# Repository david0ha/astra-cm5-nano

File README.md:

# Astra CM5 Nano

55 × 40 mm carrier board for the Raspberry Pi Compute Module 5.

## Specifications

| Item | Specification |
|---|---|
| Board size | 55 × 40 mm |
| Copper layers | 8 |
| Board thickness | 1.5936 mm |
| Module | Raspberry Pi CM5 / CM5 Lite |
| USB-C | 5 V input and USB 2.0 device port |
| USB Type-A | USB 3.0 host port |
| CSI / DSI | Two 22-pin, four-lane ports |
| GPIO | 40-pin SMT header; 3.3 V reference by default (R16 fitted, R17 DNP). For 1.8 V, remove R16 and fit R17; never fit both. |
| microSD | For CM5 Lite |
| Auxiliary connectors | Four-pin fan and two-pin RTC battery |
| Controls and indicators | BOOT and PWR buttons; power and activity LEDs |
| Status | Not built or tested. |

## Files

| File | Location |
|---|---|
| Native KiCad project | [hardware/cm5-nano-compatible/](hardware/cm5-nano-compatible/) |
| Full schematic | [PDF](docs/exports/schematic-full.pdf) · [SVG](docs/exports/schematic-full.svg) · [PNG](docs/exports/schematic-full.png) |
| Focused schematic pages | [PDF](docs/exports/schematic-focused-pages.pdf) |
| PCB layers | [PDF](docs/exports/pcb-layers.pdf) · [SVG](docs/exports/pcb-layers/layers.svg) · [copper-layer SVGs](docs/exports/copper-layers/) |
| Bill of materials | [Detail CSV](assembly/cm5-nano-compatible-BOM-detail.csv) · [JLCPCB CSV](assembly/cm5-nano-compatible-BOM-JLCPCB.csv) |
| Component positions | [CPL CSV](assembly/cm5-nano-compatible-CPL-kicad-native.csv); KiCad-native placement coordinates, no assembler-specific adjustments |

Vendor 3D models are not included.

Open `hardware/cm5-nano-compatible/cm5-nano-compatible.kicad_pro` in KiCad 10.

Reference: [Waveshare CM5-NANO-A](https://www.waveshare.com/cm5-nano-a.htm).

## License

Original project contributions: [CERN-OHL-P-2.0](LICENSE). Third-party material retains its original terms; see [THIRD_PARTY.md](THIRD_PARTY.md) and [LICENSES/](LICENSES/).

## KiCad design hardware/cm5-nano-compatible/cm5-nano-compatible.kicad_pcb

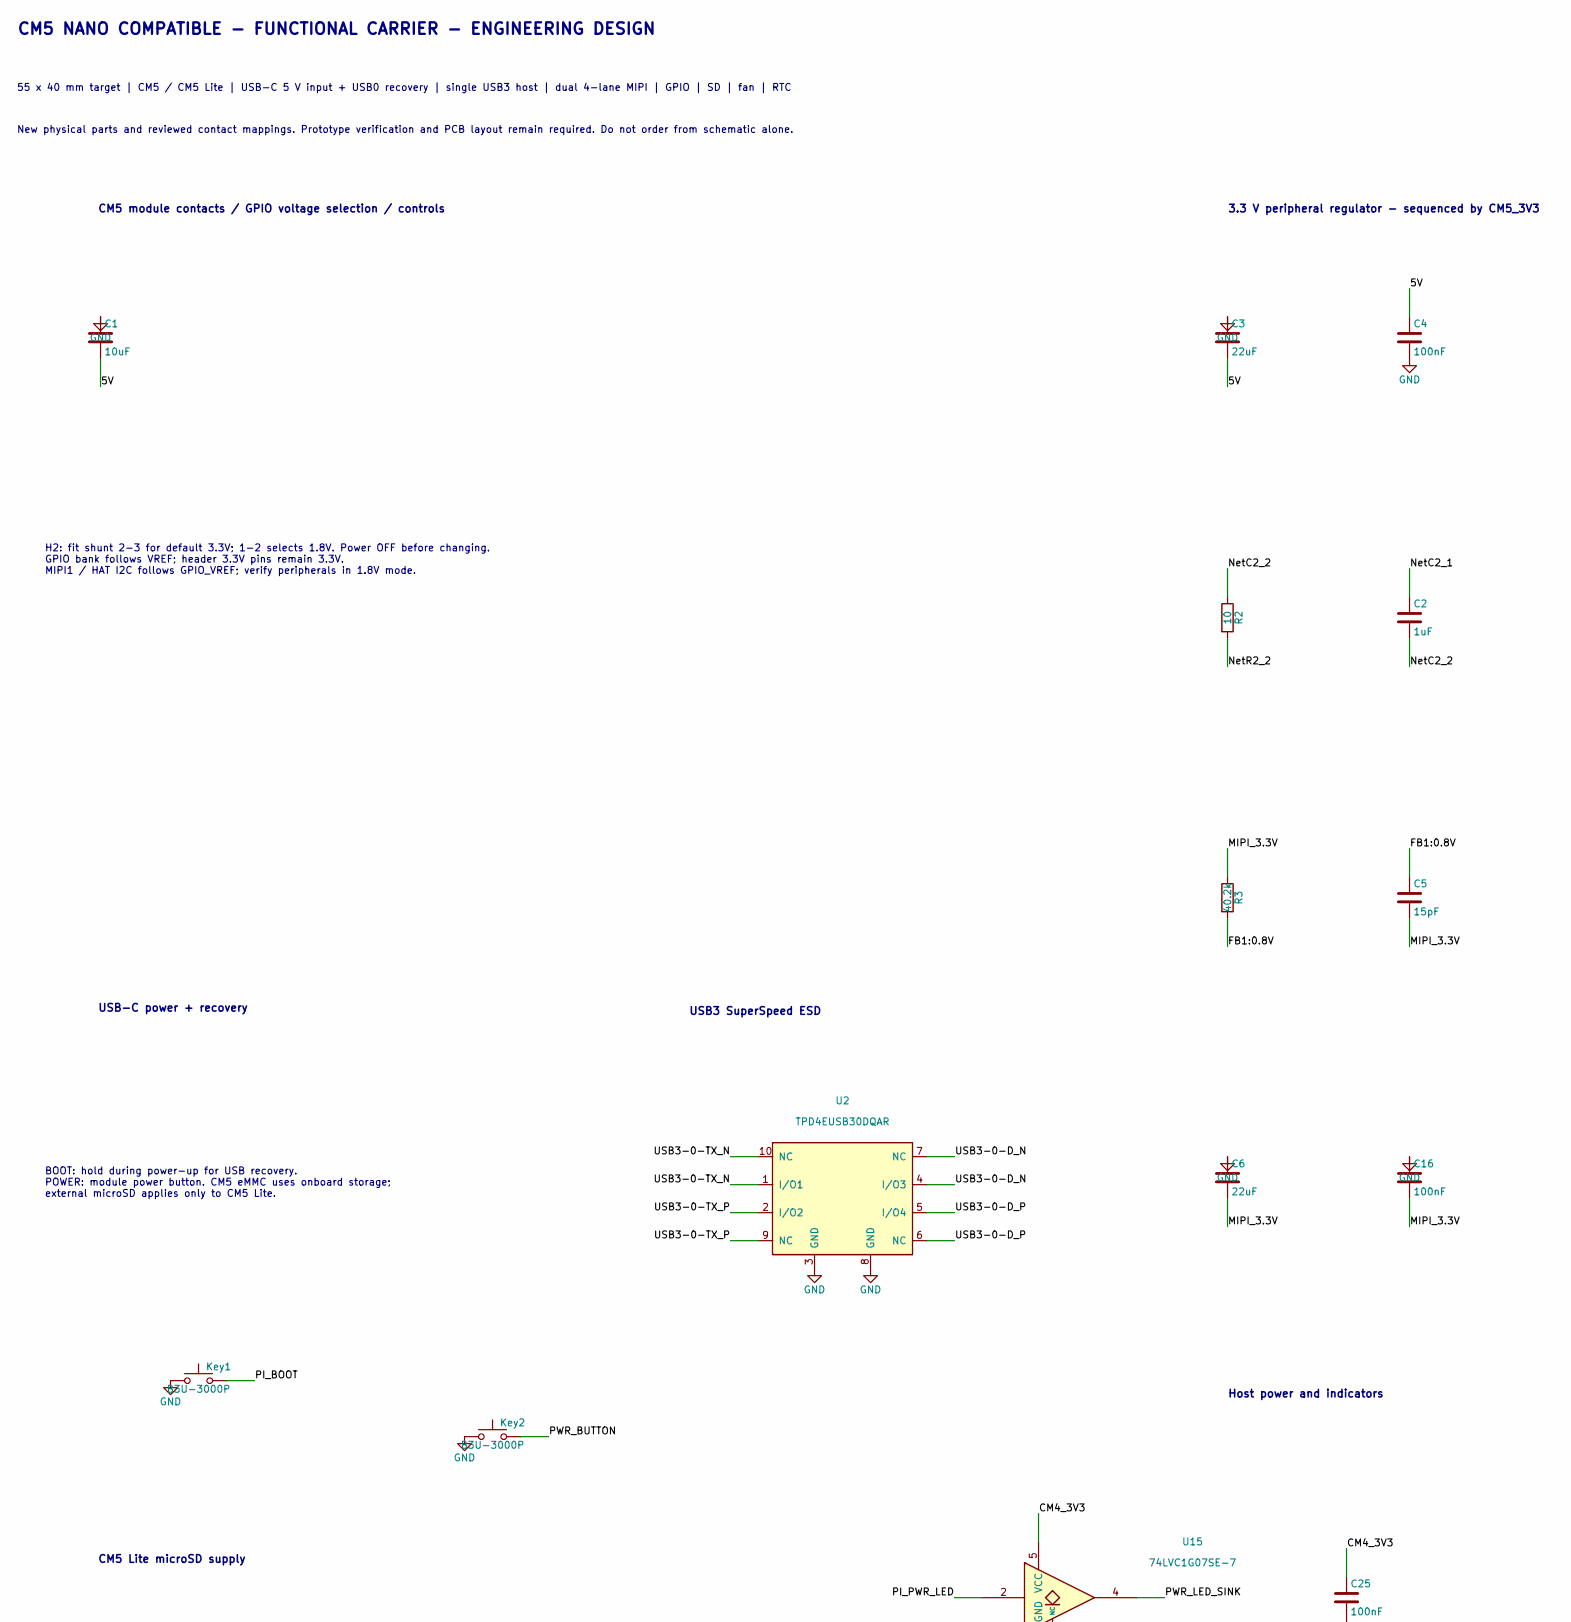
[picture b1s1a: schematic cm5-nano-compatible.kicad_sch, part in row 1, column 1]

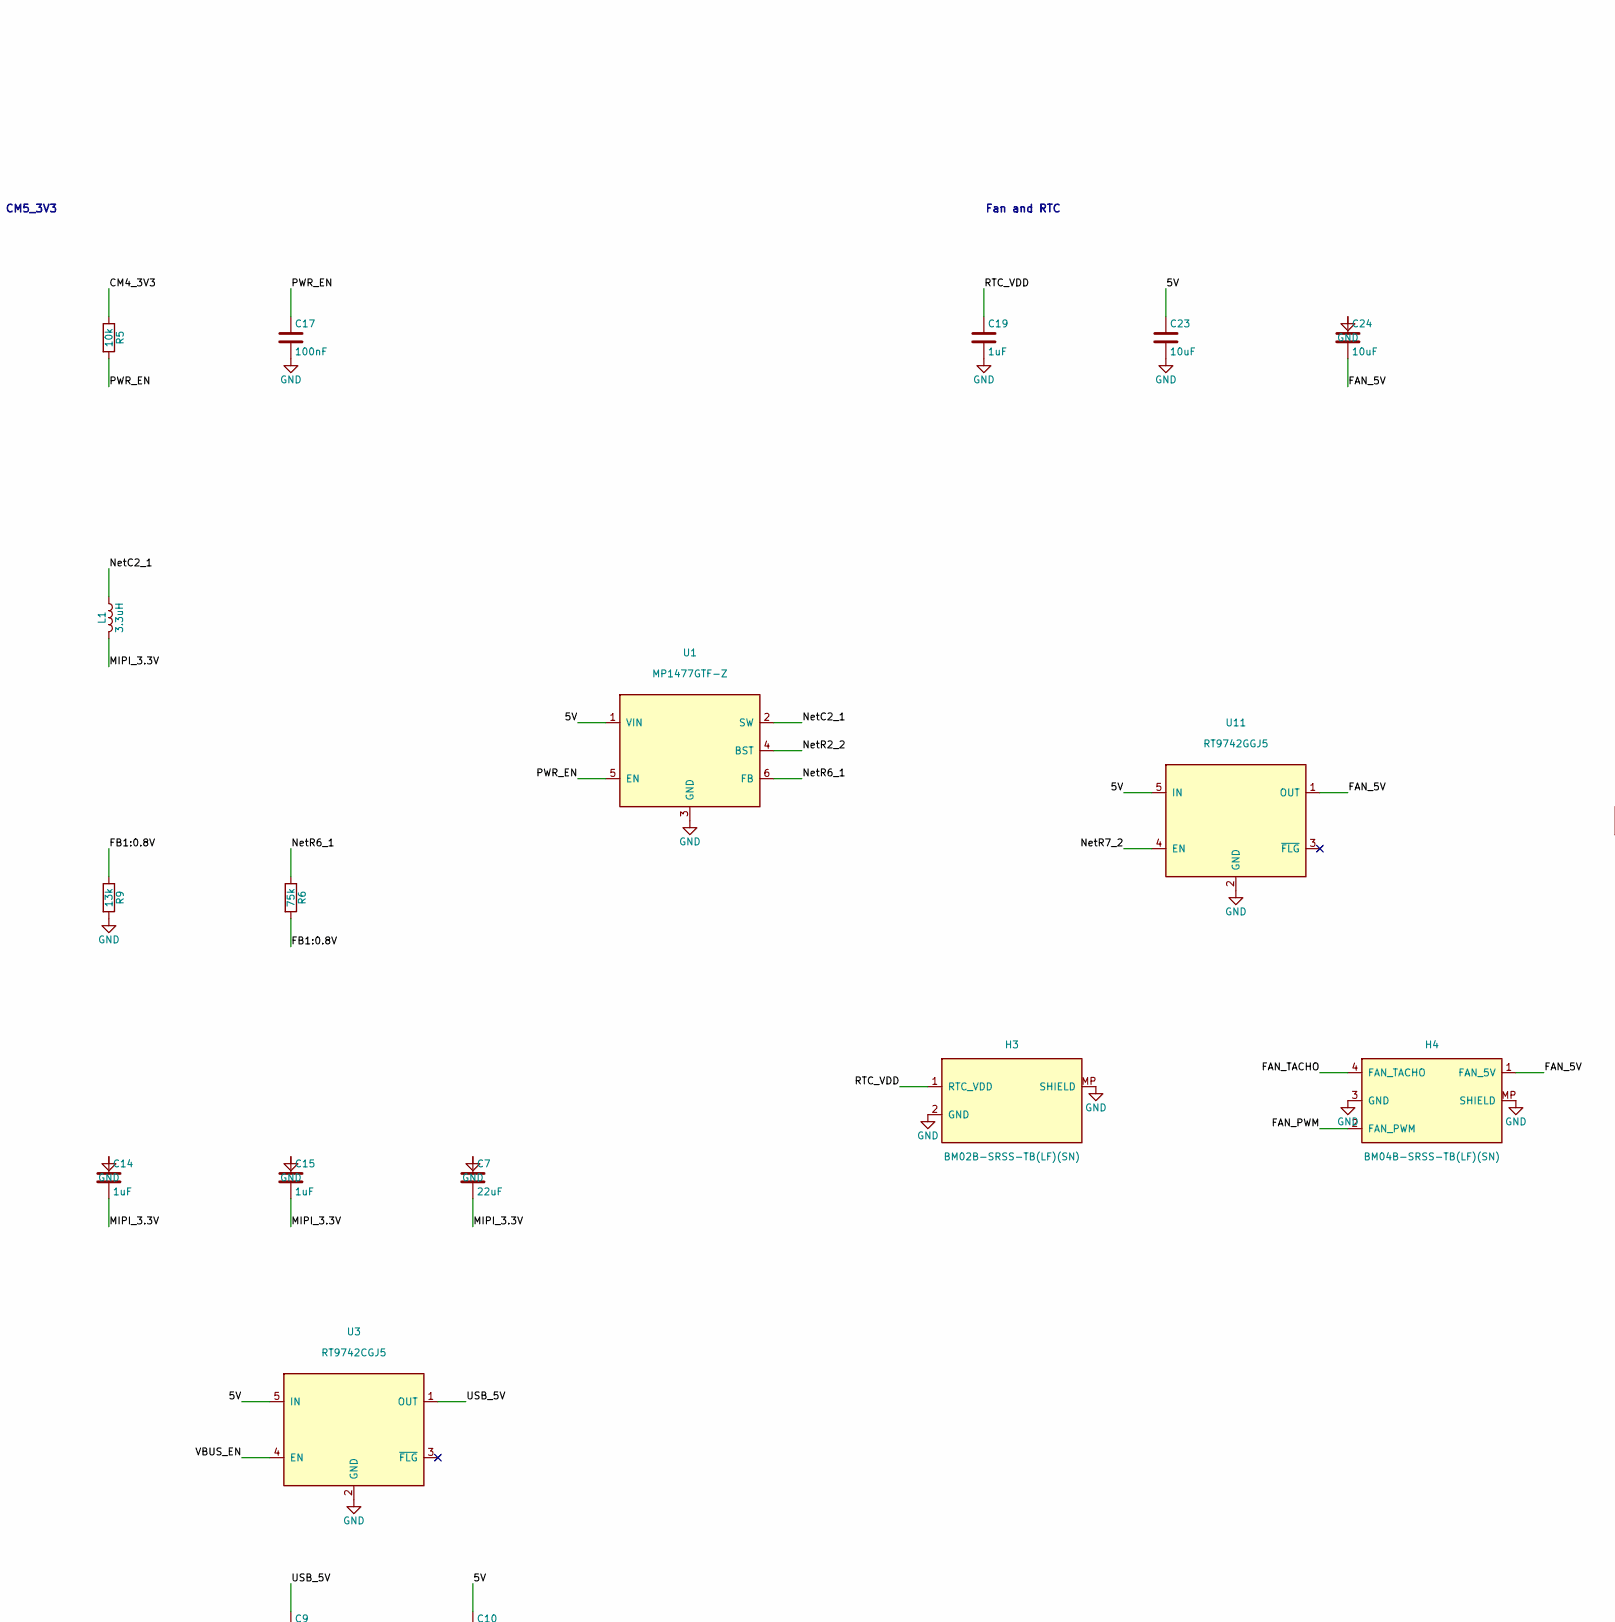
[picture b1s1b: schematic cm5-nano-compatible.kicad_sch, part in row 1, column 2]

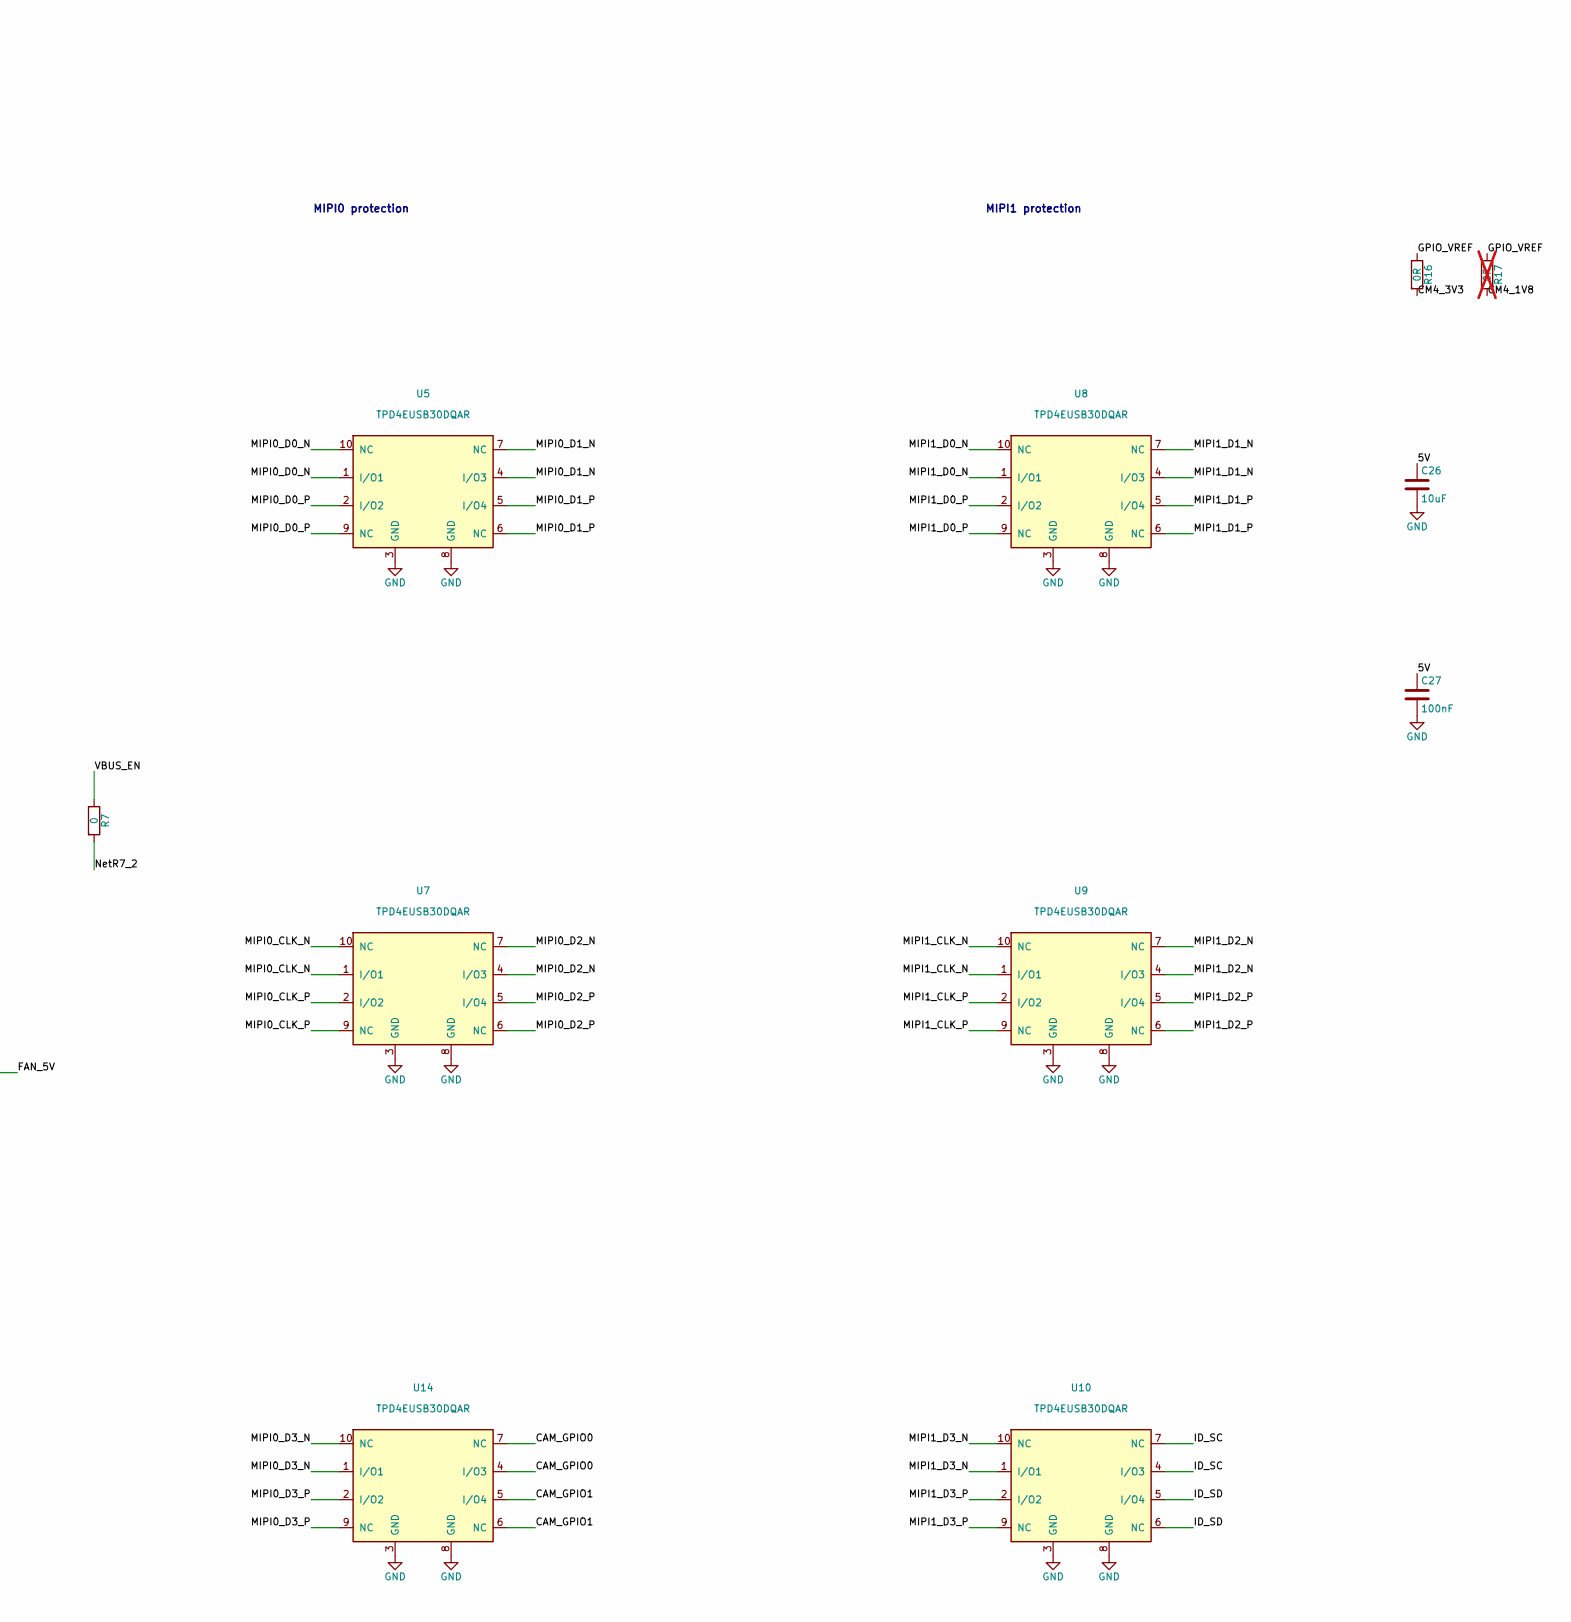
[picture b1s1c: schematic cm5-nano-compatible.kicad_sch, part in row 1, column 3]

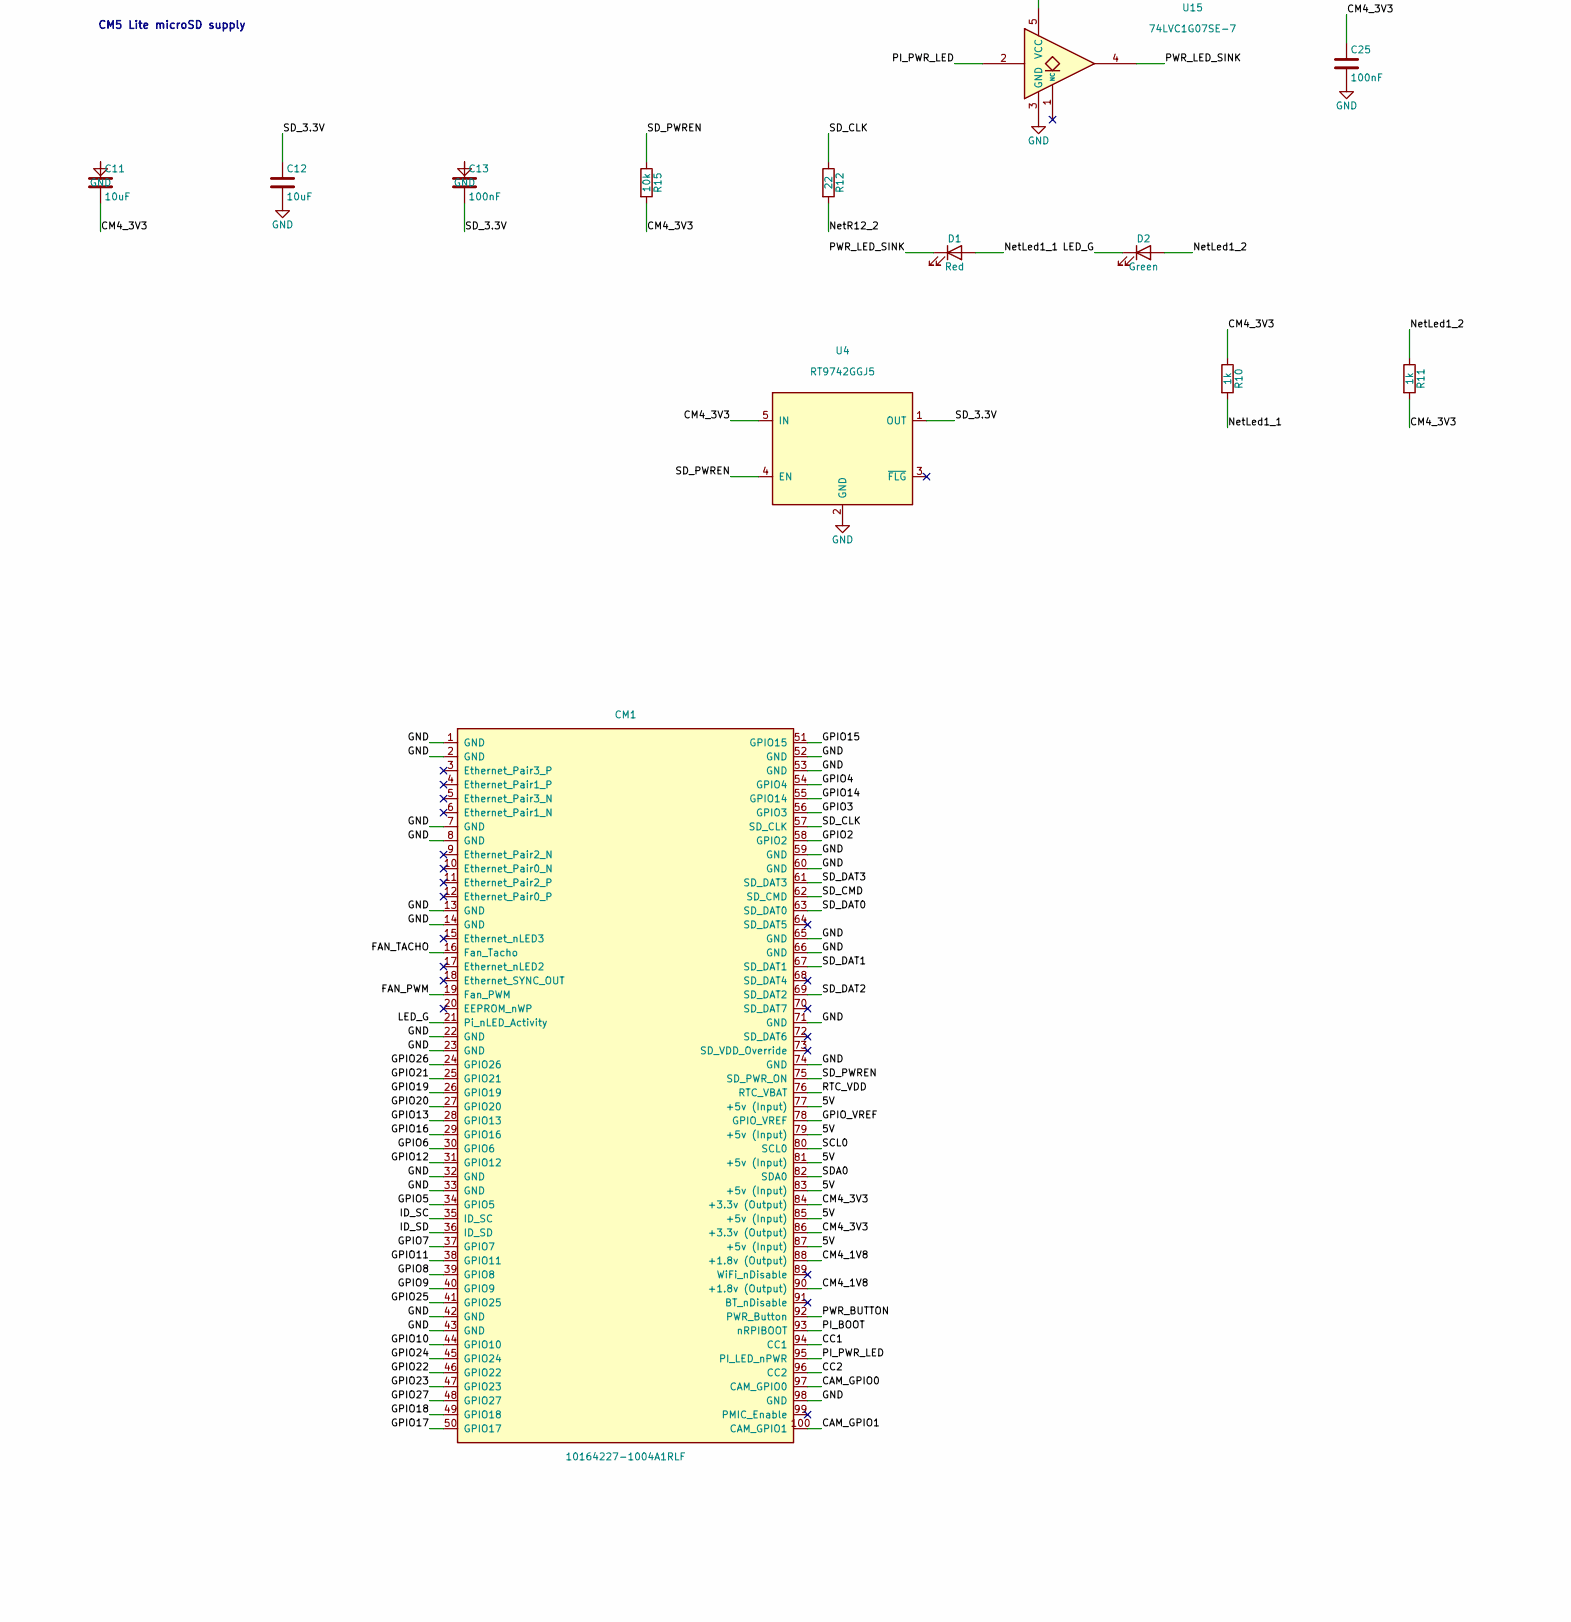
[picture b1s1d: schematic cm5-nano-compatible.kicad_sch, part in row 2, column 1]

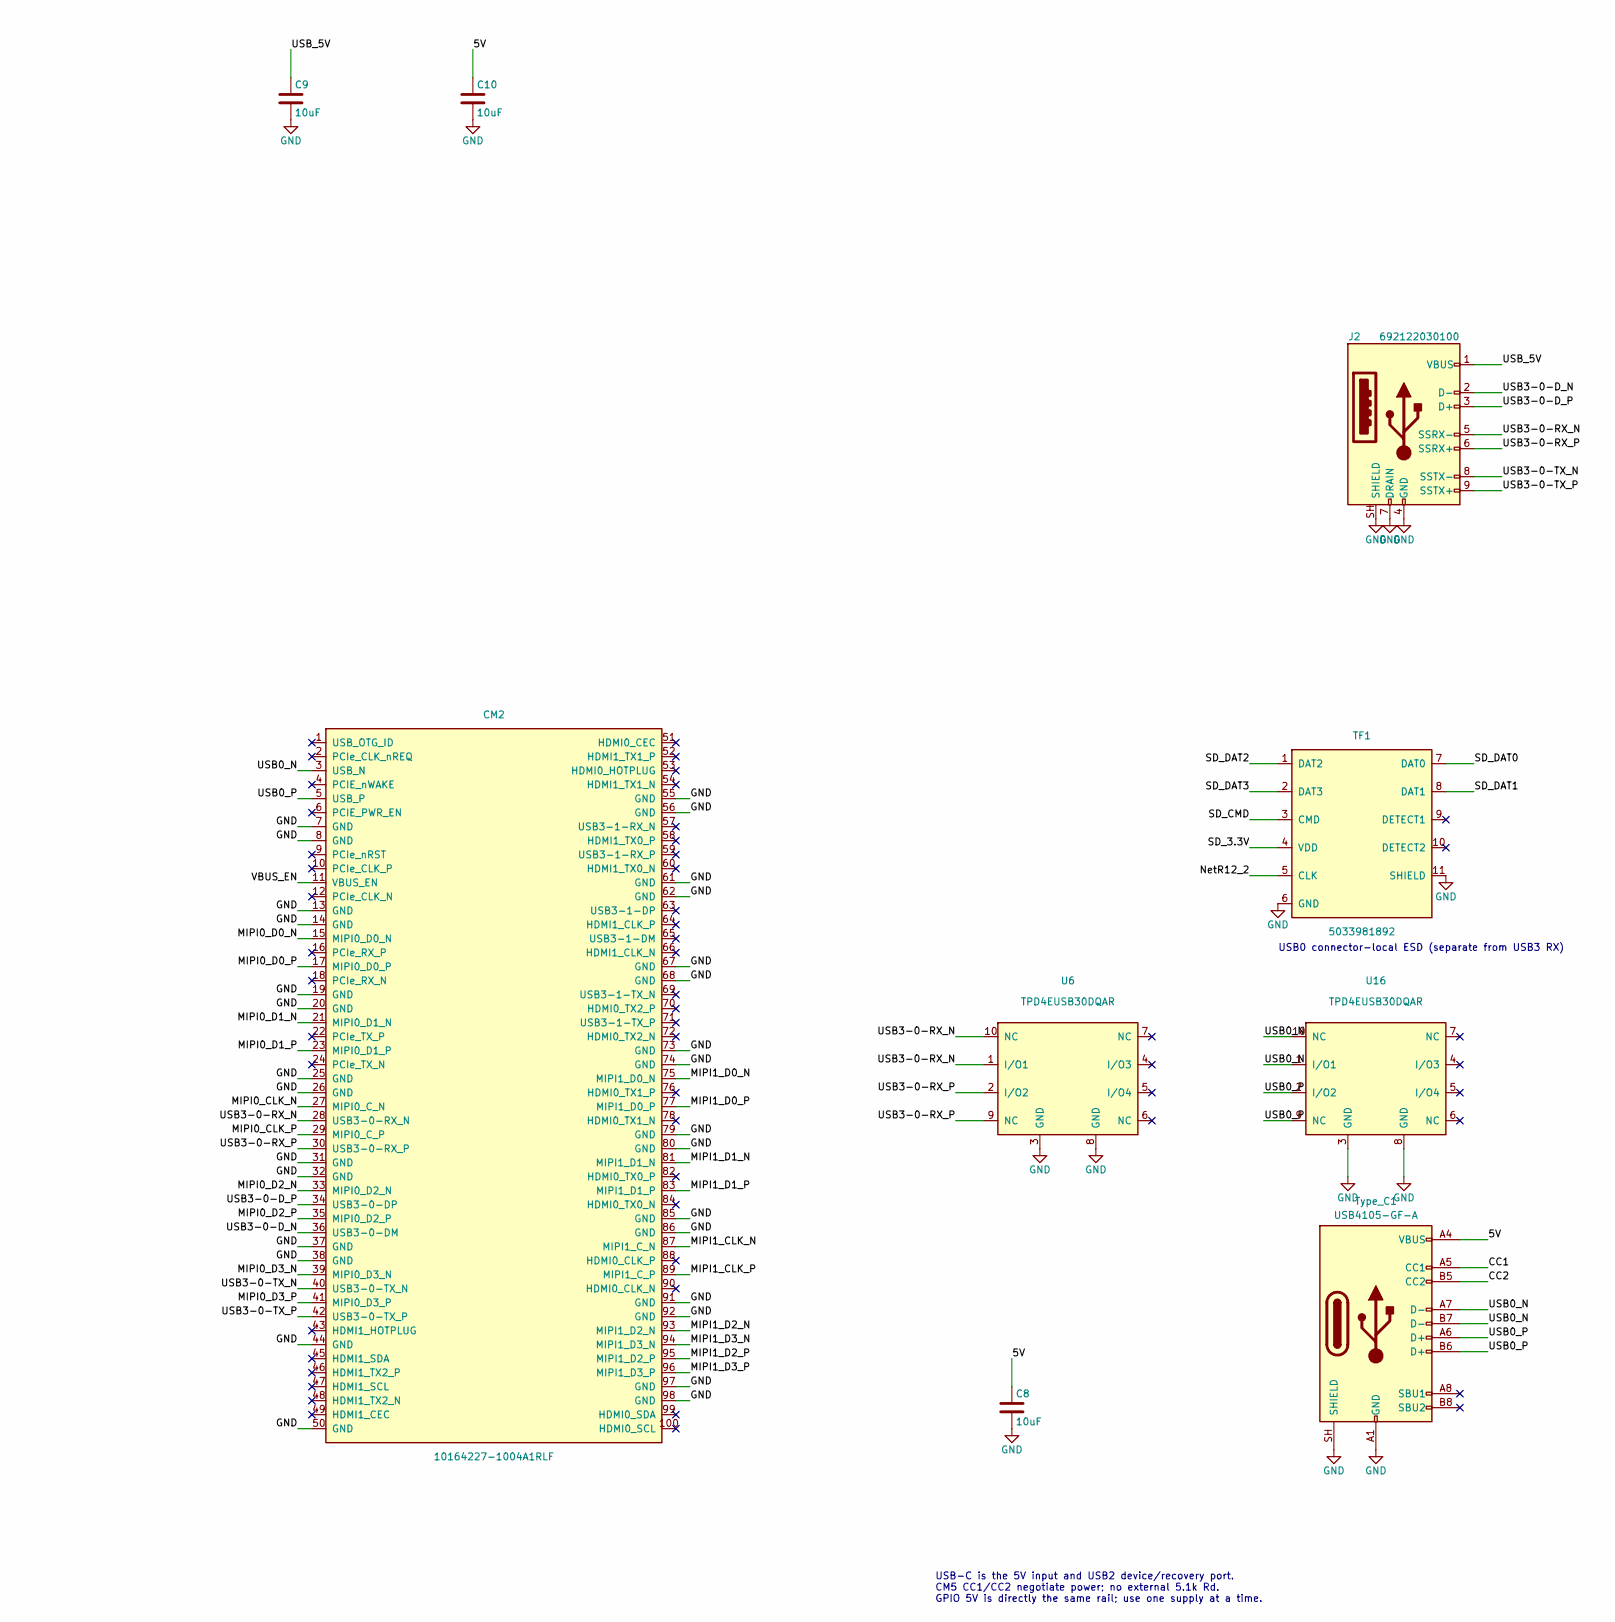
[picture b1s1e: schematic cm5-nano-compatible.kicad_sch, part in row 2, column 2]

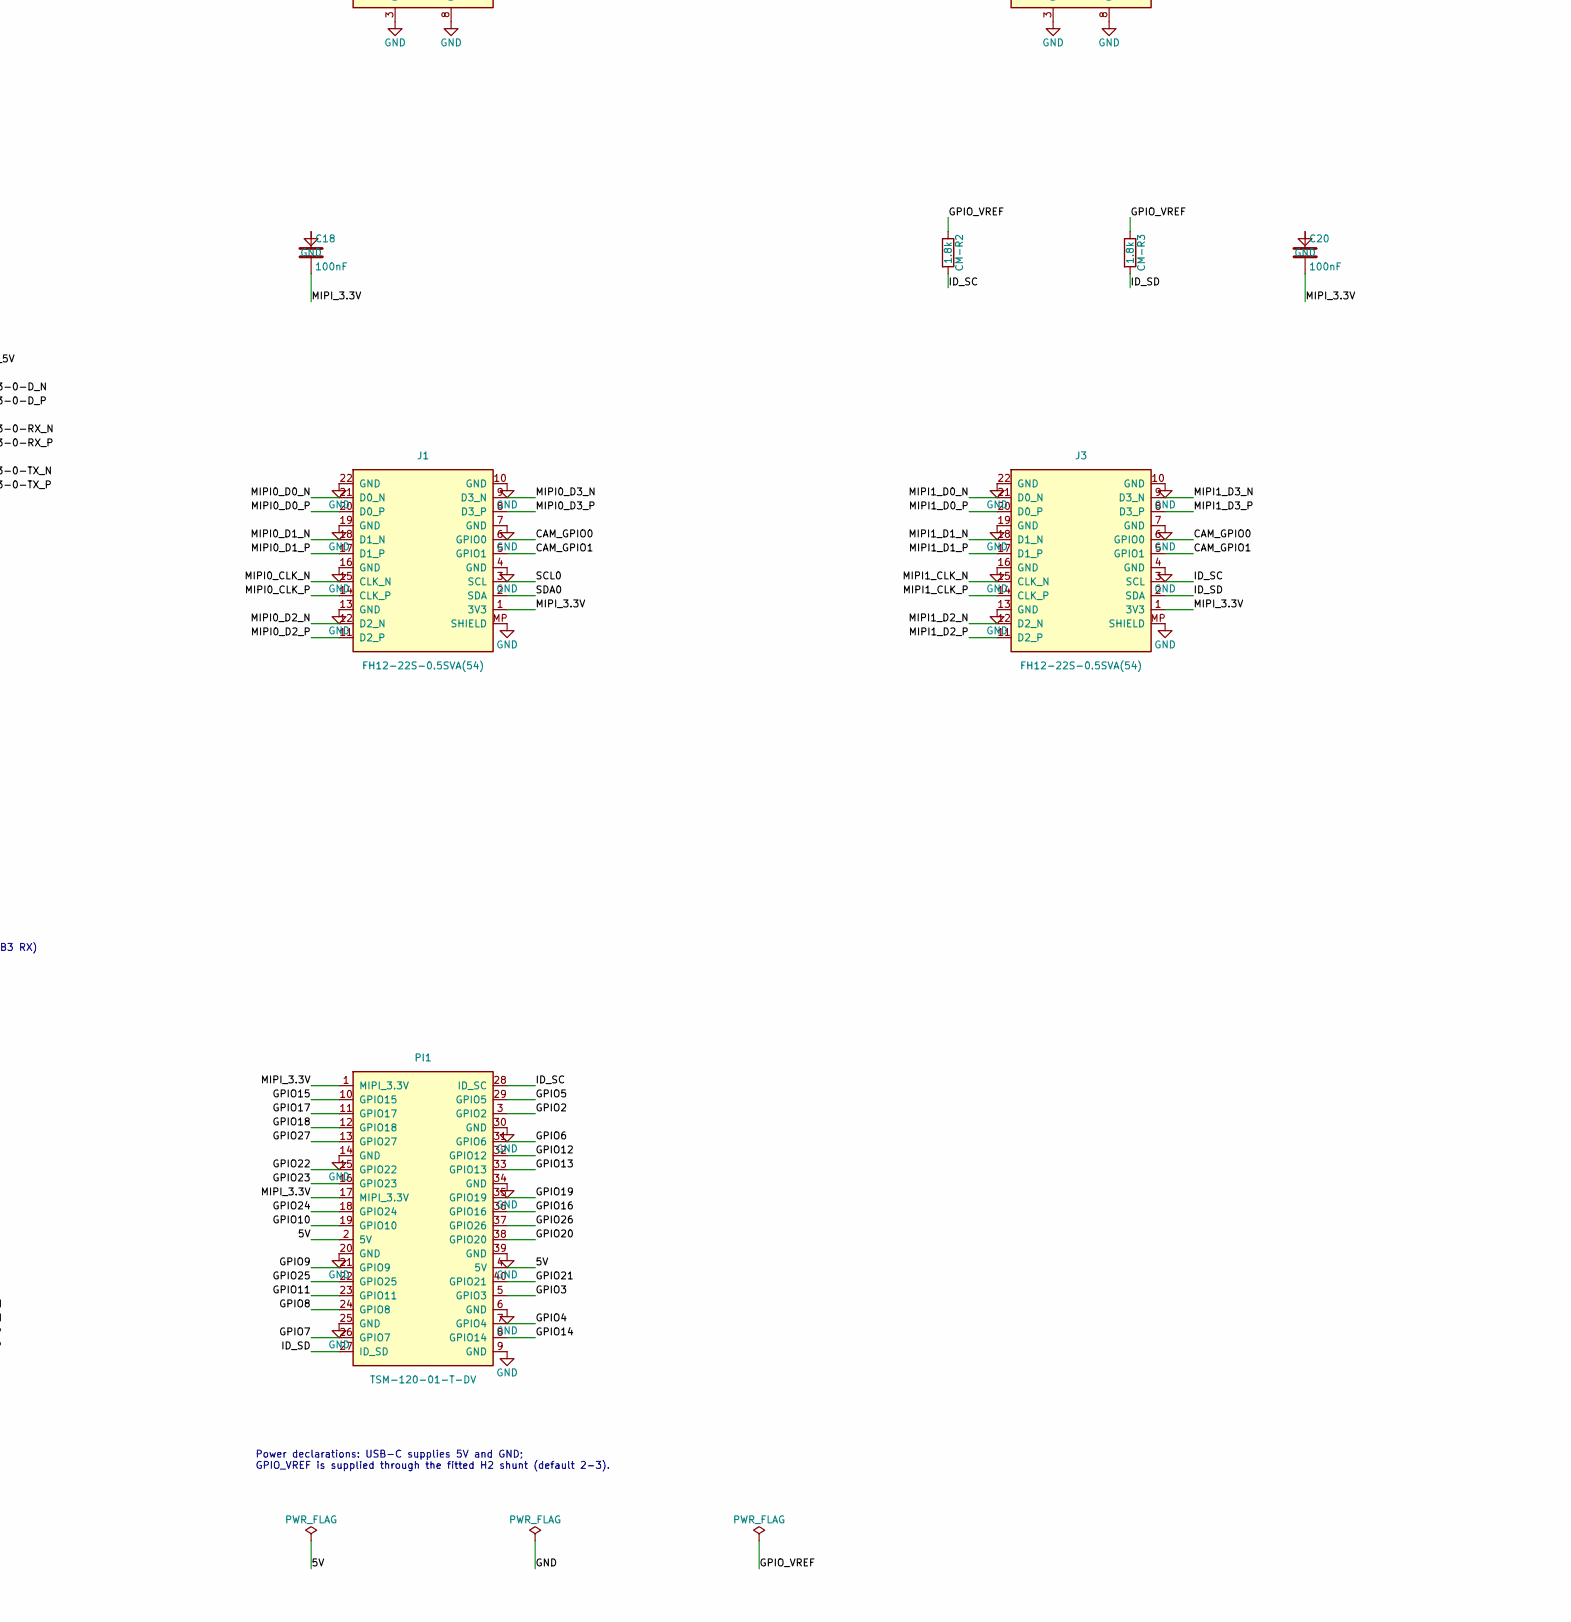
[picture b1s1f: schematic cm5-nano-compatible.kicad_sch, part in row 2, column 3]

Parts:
C1, C8, C9, C10, C11, C12, C23, C24, C26: 10uF; C_0805_2012Metric; MPN GRM21BR61A106KE19L; LCSC C77073
C2, C14, C15, C19: 1uF; C_0603_1608Metric; MPN GRM188R61A105KA61D; LCSC C86012
C3, C6, C7: 22uF; C_0805_2012Metric; MPN CL21A226MQQNNNE; LCSC C5674
C4, C13, C16, C17, C18, C20, C25, C27: 100nF; C_0603_1608Metric; MPN GRM188R71C104KA01D; LCSC C45000
C5: 15pF; C_0603_1608Metric; MPN CL10C150JB8NNNC; LCSC C1644
CM1, CM2: 10164227-1004A1RLF; Amphenol_10164227_1004A1RLF; MPN 10164227-1004A1RLF; LCSC C7435219
CM-R2, CM-R3: 1.8k; R_0402_1005Metric; MPN RC0402FR-071K8L; LCSC C163481
D1: Red; LED_0603_1608Metric; MPN LTST-C190KRKT; LCSC C94869
D2: Green; LED_0603_1608Metric; MPN LTST-C190KGKT; LCSC C125094
H3: BM02B-SRSS-TB(LF)(SN); JST_SH_BM02B-SRSS-TB_1x02-1MP_P1.00mm_Vertical; MPN BM02B-SRSS-TB(LF)(SN); LCSC C160388
H4: BM04B-SRSS-TB(LF)(SN); JST_SH_BM04B-SRSS-TB_1x04-1MP_P1.00mm_Vertical; MPN BM04B-SRSS-TB(LF)(SN); LCSC C160390
J1, J3: FH12-22S-0.5SVA(54); Hirose_FH12-22S-0.5SVA_22P_Vertical; MPN FH12-22S-0.5SVA(54); JLCPCB_PN C6250833
J2: 692122030100; USB3_A_Receptacle_Wuerth_692122030100_silk; MPN 692122030100; LCSC C5355286
Key1, Key2: B3U-3000P; SW_SPST_B3U-3000P; MPN B3U-3000P; JLCPCB_PN C963349
L1: 3.3uH; L_Coilcraft_XAL5030-XXX; MPN XAL5030-332MEC; LCSC C5342047
PI1: TSM-120-01-T-DV; Samtec_TSM-120-01-L-DV-P-TR_2x20_P2.54mm; MPN TSM-120-01-T-DV; LCSC C6723336
R2: 10; R_0402_1005Metric; MPN RC0402FR-0710RL; LCSC C138066
R3: 40.2k; R_0402_1005Metric; MPN RC0402FR-0740K2L; LCSC C137983
R5, R15: 10k; R_0402_1005Metric; MPN RC0402FR-0710KL; LCSC C60490
R6: 75k; R_0402_1005Metric; MPN RC0402FR-0775KL; LCSC C137935
R7: 0; R_0402_1005Metric; MPN RC0402JR-070RL; LCSC C60485
R9: 13k; R_0402_1005Metric; MPN RC0402FR-0713KL; LCSC C138057
R10, R11: 1k; R_0402_1005Metric; MPN RC0402FR-071KL; LCSC C106235
R12: 22; R_0402_1005Metric; MPN RC0402FR-0722RL; LCSC C114765
R16: 0R; R_0402_1005Metric; MPN RC0402FR-070RL; LCSC C106231
R17: 0R; R_0402_1005Metric; MPN RC0402FR-070RL; LCSC C106231; not fitted
TF1: 5033981892; SDCARD_MOLEX_503398-1892; MPN 5033981892; LCSC C428492
Type_C1: USB4105-GF-A; USB_C_GCT_USB4105_GroundClearance_020; MPN USB4105-GF-A; LCSC C3020560
U1: MP1477GTF-Z; MP1658_SOT563_MPS; MPN MP1477GTF-Z; LCSC C3193189
U2, U5, U6, U7, U8, U10, U14, U16: TPD4EUSB30DQAR; TI_TPD4EUSB30_DQA0010A; MPN TPD4EUSB30DQAR; LCSC C90627
U3: RT9742CGJ5; SOT-23-5; MPN RT9742CGJ5; LCSC C250546
U4, U11: RT9742GGJ5; SOT-23-5; MPN RT9742GGJ5; LCSC C250547
U9: TPD4EUSB30DQAR; TI_TPD4EUSB30_DQA0010A_U9; MPN TPD4EUSB30DQAR; LCSC C90627
U15: 74LVC1G07SE-7; 74LVC1G07_SOT353_Diodes; MPN 74LVC1G07SE-7; LCSC C67531

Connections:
/5V: C1.2, C3.2, C4.1, C8.1, C10.1, C23.1, C26.1, C27.1, CM1.77 (+5v (Input)), CM1.79 (+5v (Input)), CM1.81 (+5v (Input)), CM1.83 (+5v (Input)), CM1.85 (+5v (Input)), CM1.87 (+5v (Input)), PI1.2 (5V), PI1.4 (5V), Type_C1.A4 (VBUS), Type_C1.A9 (VBUS), Type_C1.B4 (VBUS), Type_C1.B9 (VBUS), U1.1 (VIN), U3.5 (IN), U11.5 (IN)
/CAM_GPIO0: CM1.97 (CAM_GPIO0), J1.6 (GPIO0), J3.6 (GPIO0), U14.4 (I/O3), U14.7 (NC)
/CAM_GPIO1: CM1.100 (CAM_GPIO1), J1.5 (GPIO1), J3.5 (GPIO1), U14.5 (I/O4), U14.6 (NC)
/CC1: CM1.94 (CC1), Type_C1.A5 (CC1)
/CC2: CM1.96 (CC2), Type_C1.B5 (CC2)
/CM4_1V8: CM1.88 (+1.8v (Output)), CM1.90 (+1.8v (Output)), R17.2
/CM4_3V3: C11.2, C25.1, CM1.84 (+3.3v (Output)), CM1.86 (+3.3v (Output)), R5.1, R10.1, R11.2, R15.2, R16.2, U4.5 (IN), U15.5 (VCC)
/FAN_5V: C24.2, H4.1 (FAN_5V), U11.1 (OUT)
/FAN_PWM: CM1.19 (Fan_PWM), H4.2 (FAN_PWM)
/FAN_TACHO: CM1.16 (Fan_Tacho), H4.4 (FAN_TACHO)
/FB1:0.8V: C5.1, R3.2, R6.2, R9.1
/GPIO2: CM1.58 (GPIO2), PI1.3 (GPIO2)
/GPIO3: CM1.56 (GPIO3), PI1.5 (GPIO3)
/GPIO4: CM1.54 (GPIO4), PI1.7 (GPIO4)
/GPIO5: CM1.34 (GPIO5), PI1.29 (GPIO5)
/GPIO6: CM1.30 (GPIO6), PI1.31 (GPIO6)
/GPIO7: CM1.37 (GPIO7), PI1.26 (GPIO7)
/GPIO8: CM1.39 (GPIO8), PI1.24 (GPIO8)
/GPIO9: CM1.40 (GPIO9), PI1.21 (GPIO9)
/GPIO10: CM1.44 (GPIO10), PI1.19 (GPIO10)
/GPIO11: CM1.38 (GPIO11), PI1.23 (GPIO11)
/GPIO12: CM1.31 (GPIO12), PI1.32 (GPIO12)
/GPIO13: CM1.28 (GPIO13), PI1.33 (GPIO13)
/GPIO14: CM1.55 (GPIO14), PI1.8 (GPIO14)
/GPIO15: CM1.51 (GPIO15), PI1.10 (GPIO15)
/GPIO16: CM1.29 (GPIO16), PI1.36 (GPIO16)
/GPIO17: CM1.50 (GPIO17), PI1.11 (GPIO17)
/GPIO18: CM1.49 (GPIO18), PI1.12 (GPIO18)
/GPIO19: CM1.26 (GPIO19), PI1.35 (GPIO19)
/GPIO20: CM1.27 (GPIO20), PI1.38 (GPIO20)
/GPIO21: CM1.25 (GPIO21), PI1.40 (GPIO21)
/GPIO22: CM1.46 (GPIO22), PI1.15 (GPIO22)
/GPIO23: CM1.47 (GPIO23), PI1.16 (GPIO23)
/GPIO24: CM1.45 (GPIO24), PI1.18 (GPIO24)
/GPIO25: CM1.41 (GPIO25), PI1.22 (GPIO25)
/GPIO26: CM1.24 (GPIO26), PI1.37 (GPIO26)
/GPIO27: CM1.48 (GPIO27), PI1.13 (GPIO27)
/GPIO_VREF: CM1.78 (GPIO_VREF), CM-R2.1, CM-R3.1, R16.1, R17.1
/ID_SC: CM1.35 (ID_SC), CM-R2.2, J3.3 (SCL), PI1.28 (ID_SC), U10.4 (I/O3), U10.7 (NC)
/ID_SD: CM1.36 (ID_SD), CM-R3.2, J3.2 (SDA), PI1.27 (ID_SD), U10.5 (I/O4), U10.6 (NC)
/LED_G: CM1.21 (Pi_nLED_Activity), D2.1 (K)
/MIPI0_CLK_N: CM2.27 (MIPI0_C_N), J1.15 (CLK_N), U7.1 (I/O1), U7.10 (NC)
/MIPI0_CLK_P: CM2.29 (MIPI0_C_P), J1.14 (CLK_P), U7.2 (I/O2), U7.9 (NC)
/MIPI0_D0_N: CM2.15 (MIPI0_D0_N), J1.21 (D0_N), U5.1 (I/O1), U5.10 (NC)
/MIPI0_D0_P: CM2.17 (MIPI0_D0_P), J1.20 (D0_P), U5.2 (I/O2), U5.9 (NC)
/MIPI0_D1_N: CM2.21 (MIPI0_D1_N), J1.18 (D1_N), U5.4 (I/O3), U5.7 (NC)
/MIPI0_D1_P: CM2.23 (MIPI0_D1_P), J1.17 (D1_P), U5.5 (I/O4), U5.6 (NC)
/MIPI0_D2_N: CM2.33 (MIPI0_D2_N), J1.12 (D2_N), U7.4 (I/O3), U7.7 (NC)
/MIPI0_D2_P: CM2.35 (MIPI0_D2_P), J1.11 (D2_P), U7.5 (I/O4), U7.6 (NC)
/MIPI0_D3_N: CM2.39 (MIPI0_D3_N), J1.9 (D3_N), U14.1 (I/O1), U14.10 (NC)
/MIPI0_D3_P: CM2.41 (MIPI0_D3_P), J1.8 (D3_P), U14.2 (I/O2), U14.9 (NC)
/MIPI1_CLK_N: CM2.87 (MIPI1_C_N), J3.15 (CLK_N), U9.1 (I/O1), U9.10 (NC)
/MIPI1_CLK_P: CM2.89 (MIPI1_C_P), J3.14 (CLK_P), U9.2 (I/O2), U9.9 (NC)
/MIPI1_D0_N: CM2.75 (MIPI1_D0_N), J3.21 (D0_N), U8.1 (I/O1), U8.10 (NC)
/MIPI1_D0_P: CM2.77 (MIPI1_D0_P), J3.20 (D0_P), U8.2 (I/O2), U8.9 (NC)
/MIPI1_D1_N: CM2.81 (MIPI1_D1_N), J3.18 (D1_N), U8.4 (I/O3), U8.7 (NC)
/MIPI1_D1_P: CM2.83 (MIPI1_D1_P), J3.17 (D1_P), U8.5 (I/O4), U8.6 (NC)
/MIPI1_D2_N: CM2.93 (MIPI1_D2_N), J3.12 (D2_N), U9.4 (I/O3), U9.7 (NC)
/MIPI1_D2_P: CM2.95 (MIPI1_D2_P), J3.11 (D2_P), U9.5 (I/O4), U9.6 (NC)
/MIPI1_D3_N: CM2.94 (MIPI1_D3_N), J3.9 (D3_N), U10.1 (I/O1), U10.10 (NC)
/MIPI1_D3_P: CM2.96 (MIPI1_D3_P), J3.8 (D3_P), U10.2 (I/O2), U10.9 (NC)
/MIPI_3.3V: C5.2, C6.2, C7.2, C14.2, C15.2, C16.2, C18.2, C20.2, J1.1 (3V3), J3.1 (3V3), L1.2, PI1.1 (MIPI_3.3V), PI1.17 (MIPI_3.3V), R3.1
/NetC2_1: C2.1, L1.1, U1.2 (SW)
/NetC2_2: C2.2, R2.1
/NetLed1_1: D1.2 (A), R10.2
/NetLed1_2: D2.2 (A), R11.1
/NetR2_2: R2.2, U1.4 (BST)
/NetR6_1: R6.1, U1.6 (FB)
/NetR7_2: R7.2, U11.4 (EN)
/NetR12_2: R12.2, TF1.5 (CLK)
/PI_BOOT: CM1.93 (nRPIBOOT), Key1.2
/PI_PWR_LED: CM1.95 (PI_LED_nPWR), U15.2
/PWR_BUTTON: CM1.92 (PWR_Button), Key2.2
/PWR_EN: C17.1, R5.2, U1.5 (EN)
/PWR_LED_SINK: D1.1 (K), U15.4
/RTC_VDD: C19.1, CM1.76 (RTC_VBAT), H3.1 (RTC_VDD)
/SCL0: CM1.80 (SCL0), J1.3 (SCL)
/SDA0: CM1.82 (SDA0), J1.2 (SDA)
/SD_3.3V: C12.1, C13.2, TF1.4 (VDD), U4.1 (OUT)
/SD_CLK: CM1.57 (SD_CLK), R12.1
/SD_CMD: CM1.62 (SD_CMD), TF1.3 (CMD)
/SD_DAT0: CM1.63 (SD_DAT0), TF1.7 (DAT0)
/SD_DAT1: CM1.67 (SD_DAT1), TF1.8 (DAT1)
/SD_DAT2: CM1.69 (SD_DAT2), TF1.1 (DAT2)
/SD_DAT3: CM1.61 (SD_DAT3), TF1.2 (DAT3)
/SD_PWREN: CM1.75 (SD_PWR_ON), R15.1, U4.4 (EN)
/USB0_N: CM2.3 (USB_N), Type_C1.A7 (D-), Type_C1.B7 (D-), U16.1 (I/O1), U16.10 (NC)
/USB0_P: CM2.5 (USB_P), Type_C1.A6 (D+), Type_C1.B6 (D+), U16.2 (I/O2), U16.9 (NC)
/USB3-0-D_N: CM2.36 (USB3-0-DM), J2.2 (D-), U2.4 (I/O3), U2.7 (NC)
/USB3-0-D_P: CM2.34 (USB3-0-DP), J2.3 (D+), U2.5 (I/O4), U2.6 (NC)
/USB3-0-RX_N: CM2.28 (USB3-0-RX_N), J2.5 (SSRX-), U6.1 (I/O1), U6.10 (NC)
/USB3-0-RX_P: CM2.30 (USB3-0-RX_P), J2.6 (SSRX+), U6.2 (I/O2), U6.9 (NC)
/USB3-0-TX_N: CM2.40 (USB3-0-TX_N), J2.8 (SSTX-), U2.1 (I/O1), U2.10 (NC)
/USB3-0-TX_P: CM2.42 (USB3-0-TX_P), J2.9 (SSTX+), U2.2 (I/O2), U2.9 (NC)
/USB_5V: C9.1, J2.1 (VBUS), U3.1 (OUT)
/VBUS_EN: CM2.11 (VBUS_EN), R7.1, U3.4 (EN)
GND: C1.1, C3.1, C4.2, C6.1, C7.1, C8.2, C9.2, C10.2, C11.1, C12.2, C13.1, C14.1, C15.1, C16.1, C17.2, C18.1, C19.2, C20.1, C23.2, C24.1, C25.2, C26.2, C27.2, CM1.1 (GND), CM1.2 (GND), CM1.7 (GND), CM1.8 (GND), CM1.13 (GND), CM1.14 (GND), CM1.22 (GND), CM1.23 (GND), CM1.32 (GND), CM1.33 (GND), CM1.42 (GND), CM1.43 (GND), CM1.52 (GND), CM1.53 (GND), CM1.59 (GND), CM1.60 (GND), CM1.65 (GND), CM1.66 (GND), CM1.71 (GND), CM1.74 (GND), CM1.98 (GND), CM2.7 (GND), CM2.8 (GND), CM2.13 (GND), CM2.14 (GND), CM2.19 (GND), CM2.20 (GND), CM2.25 (GND), CM2.26 (GND), CM2.31 (GND), CM2.32 (GND), CM2.37 (GND), CM2.38 (GND), CM2.44 (GND), CM2.50 (GND), CM2.55 (GND), CM2.56 (GND), CM2.61 (GND), CM2.62 (GND), CM2.67 (GND), CM2.68 (GND), CM2.73 (GND), CM2.74 (GND), CM2.79 (GND), CM2.80 (GND), CM2.85 (GND), CM2.86 (GND), CM2.91 (GND), CM2.92 (GND), CM2.97 (GND), CM2.98 (GND), H3.2 (GND), H3.MP (SHIELD), H4.3 (GND), H4.MP (SHIELD), J1.4 (GND), J1.7 (GND), J1.10 (GND), J1.13 (GND), J1.16 (GND), J1.19 (GND), J1.22 (GND), J1.MP (SHIELD), J2.4 (GND), J2.7 (DRAIN), J2.SH (SHIELD), J3.4 (GND), J3.7 (GND), J3.10 (GND), J3.13 (GND), J3.16 (GND), J3.19 (GND), J3.22 (GND), J3.MP (SHIELD), Key1.1, Key2.1, PI1.6 (GND), PI1.9 (GND), PI1.14 (GND), PI1.20 (GND), PI1.25 (GND), PI1.30 (GND), PI1.34 (GND), PI1.39 (GND), R9.2, TF1.6 (GND), TF1.11 (SHIELD), Type_C1.A1 (GND), Type_C1.A12 (GND), Type_C1.B1 (GND), Type_C1.B12 (GND), Type_C1.SH (SHIELD), U1.3 (GND), U2.3 (GND), U2.8 (GND), U3.2 (GND), U4.2 (GND), U5.3 (GND), U5.8 (GND), U6.3 (GND), U6.8 (GND), U7.3 (GND), U7.8 (GND), U8.3 (GND), U8.8 (GND), U9.3 (GND), U9.8 (GND), U10.3 (GND), U10.8 (GND), U11.2 (GND), U14.3 (GND), U14.8 (GND), U15.3 (GND), U16.3 (GND), U16.8 (GND)

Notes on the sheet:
CM5 NANO COMPATIBLE - FUNCTIONAL CARRIER - ENGINEERING DESIGN
55 x 40 mm target | CM5 / CM5 Lite | USB-C 5 V input + USB0 recovery | single USB3 host | dual 4-lane MIPI | GPIO | SD | fan | RTC
New physical parts and reviewed contact mappings. Prototype verification and PCB layout remain required. Do not order from schematic alone.
CM5 module contacts / GPIO voltage selection / controls
USB-C power + recovery
CM5 Lite microSD supply
3.3 V peripheral regulator - sequenced by CM5_3V3
Host power and indicators
Fan and RTC
MIPI0 protection
MIPI1 protection
H2: fit shunt 2-3 for default 3.3V; 1-2 selects 1.8V. Power OFF before changing. GPIO bank follows VREF; header 3.3V pins remain 3.3V. MIPI1 / HAT I2C follows GPIO_VREF; verify peripherals in 1.8V mode.
BOOT: hold during power-up for USB recovery. POWER: module power button. CM5 eMMC uses onboard storage; external microSD applies only to CM5 Lite.
USB-C is the 5V input and USB2 device/recovery port. CM5 CC1/CC2 negotiate power; no external 5.1k Rd. GPIO 5V is directly the same rail; use one supply at a time.
Power declarations: USB-C supplies 5V and GND; GPIO_VREF is supplied through the fitted H2 shunt (default 2-3).
USB3 SuperSpeed ESD
USB0 connector-local ESD (separate from USB3 RX)
